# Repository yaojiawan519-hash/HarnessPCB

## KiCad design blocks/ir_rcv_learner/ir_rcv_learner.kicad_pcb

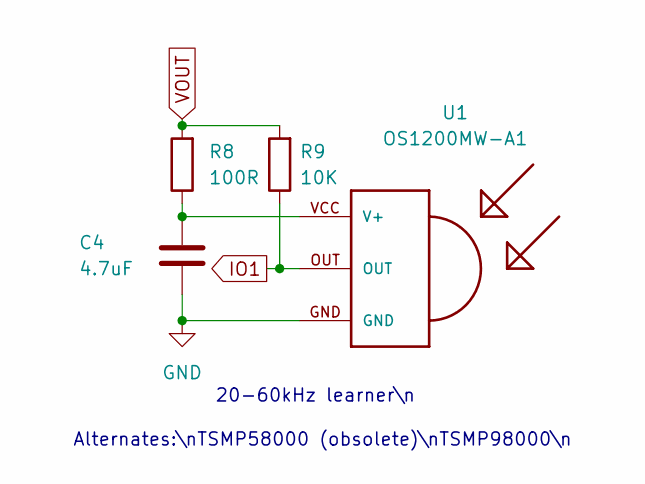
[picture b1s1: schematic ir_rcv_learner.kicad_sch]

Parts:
C4: 4.7uF; C_0805_2012Metric
R8: 100R; R_0805_2012Metric
R9: 10K; R_0805_2012Metric
U1: OS1200MW-A1; TSOP18XX

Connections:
GND: C4.2, U1.GND
IO1: R9.1, U1.OUT
unnamed: C4.1, R8.1, U1.VCC (V+)
VOUT: R8.2, R9.2

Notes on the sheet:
Alternates:\nTSMP58000 (obsolete)\nTSMP98000\n
20-60kHz learner\n

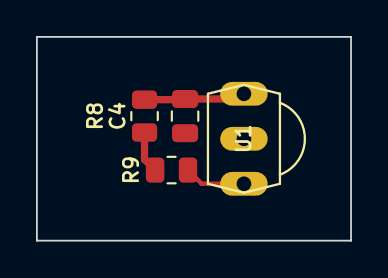
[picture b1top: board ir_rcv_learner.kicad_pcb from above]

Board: 2 copper layers, 17.5 x 11.3 mm, 4 parts (0 on the bottom side), 4 nets.

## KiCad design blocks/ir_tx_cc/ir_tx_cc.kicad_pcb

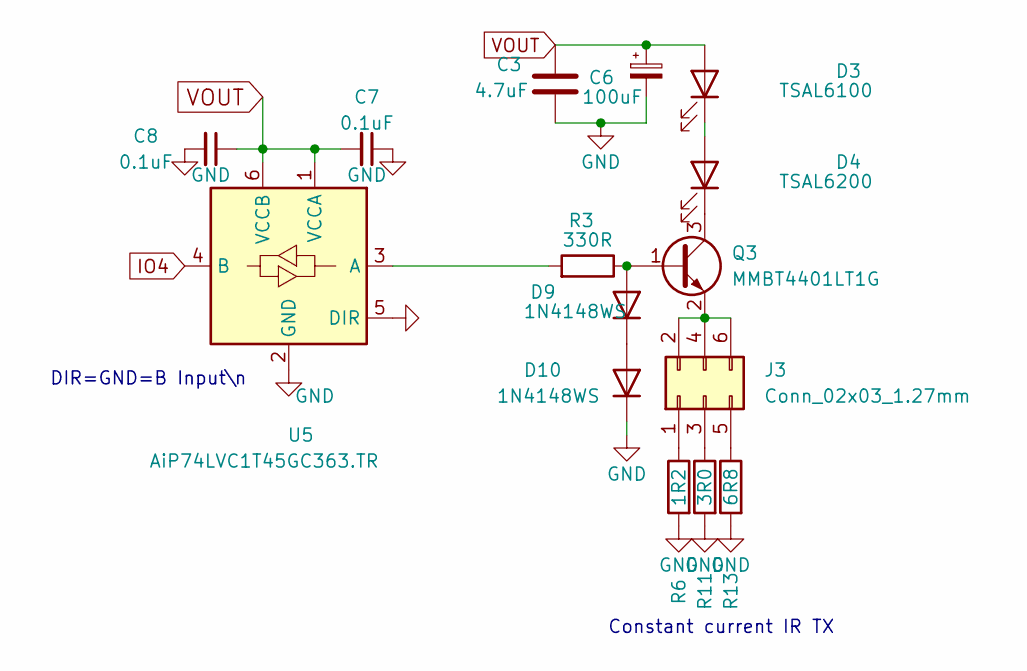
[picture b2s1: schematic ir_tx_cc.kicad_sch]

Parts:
C3: 4.7uF; C_0805_2012Metric
C6: 100uF; CP_EIA-3528-21_Kemet-B_Pad1.50x2.35mm_HandSolder
C7, C8: 0.1uF; C_0805_2012Metric
D3: TSAL6100; LED_D5.0mm_Horizontal_O1.27mm_Z3.0mm_IRGrey
D4: TSAL6200; LED_D5.0mm_Horizontal_O1.27mm_Z3.0mm_IRGrey
D9, D10: 1N4148WS; D_SOD-323F
J3: Conn_02x03_1.27mm; PinHeader_2x03_P1.27mm_Vertical
Q3: MMBT4401LT1G; SOT-23
R3: 330R; R_0805_2012Metric
R6: 1R2; R_1206_3216Metric
R11: 3R0; R_1206_3216Metric
R13: 6R8; R_1206_3216Metric
U5: AiP74LVC1T45GC363.TR; SOT-363_SC-70-6

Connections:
GND: C3.2, C6.2, C7.1, C8.2, D10.1 (K), R6.2, R11.2, R13.2, U5.2 (GND), U5.5 (DIR)
IO4: U5.4 (B)
unnamed: D3.1 (K), D4.2 (A)
unnamed: D4.1 (K), Q3.3 (C)
unnamed: D9.2 (A), Q3.1 (B), R3.1
unnamed: D9.1 (K), D10.2 (A)
unnamed: J3.1, R6.1
unnamed: J3.2, J3.4, J3.6, Q3.2 (E)
unnamed: J3.3, R11.1
unnamed: J3.5, R13.1
unnamed: R3.2, U5.3 (A)
VOUT: C3.1, C6.1, C7.2, C8.1, D3.2 (A), U5.1 (VCCA), U5.6 (VCCB)

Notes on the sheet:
Constant current IR TX
DIR=GND=B Input\n

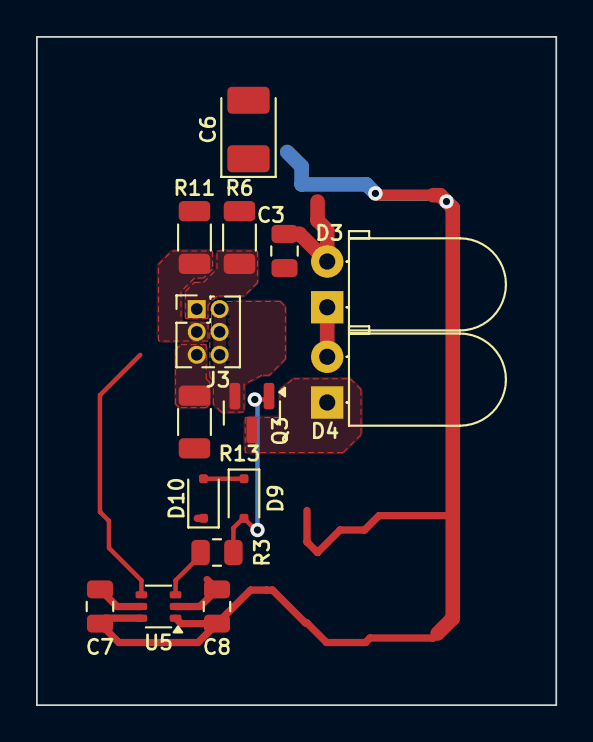
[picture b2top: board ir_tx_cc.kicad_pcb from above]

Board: 2 copper layers, 28.9 x 37.1 mm, 15 parts (0 on the bottom side), 11 nets.

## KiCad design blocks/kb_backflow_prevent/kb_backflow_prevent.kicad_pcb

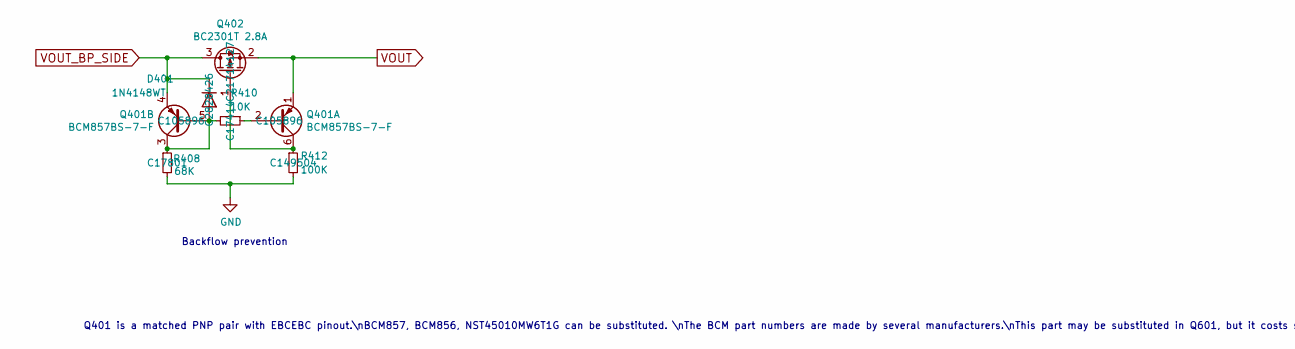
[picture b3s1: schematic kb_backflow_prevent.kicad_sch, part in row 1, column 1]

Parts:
D401: 1N4148WT; D_SOD-523
Q401: BCM857BS-7-F; SOT-363_SC-70-6
Q402: BC2301T 2.8A; SOT-523
R408: 68K; R_0805_2012Metric
R410: 10K; R_0805_2012Metric
R412: 100K; R_0805_2012Metric

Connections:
GND: R408.2, R412.2
unnamed: D401.2 (A), Q401.3 (C2), Q401.5 (B2), R408.1, R410.2
unnamed: Q401.2 (B1), R410.1
unnamed: Q401.6 (C1), Q402.1 (G), R412.1
VOUT: Q401.1 (E1), Q402.2 (S)
VOUT_BP_SIDE: D401.1 (K), Q401.4 (E2), Q402.3 (D)

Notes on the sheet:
Q401 is a matched PNP pair with EBCEBC pinout.\nBCM857, BCM856, NST45010MW6T1G can be substituted. \nThe BCM part numbers are made by several manufacturers.\nThis part may be substituted in Q601, but it costs significantly more.\n\nDMMT3906, PMP5201, PMP5501 are similar but have a BBCEEC pinout.\nT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
Backflow prevention

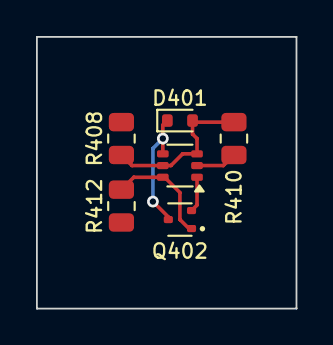
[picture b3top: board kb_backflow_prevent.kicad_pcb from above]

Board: 2 copper layers, 14.4 x 15.1 mm, 6 parts (0 on the bottom side), 6 nets.

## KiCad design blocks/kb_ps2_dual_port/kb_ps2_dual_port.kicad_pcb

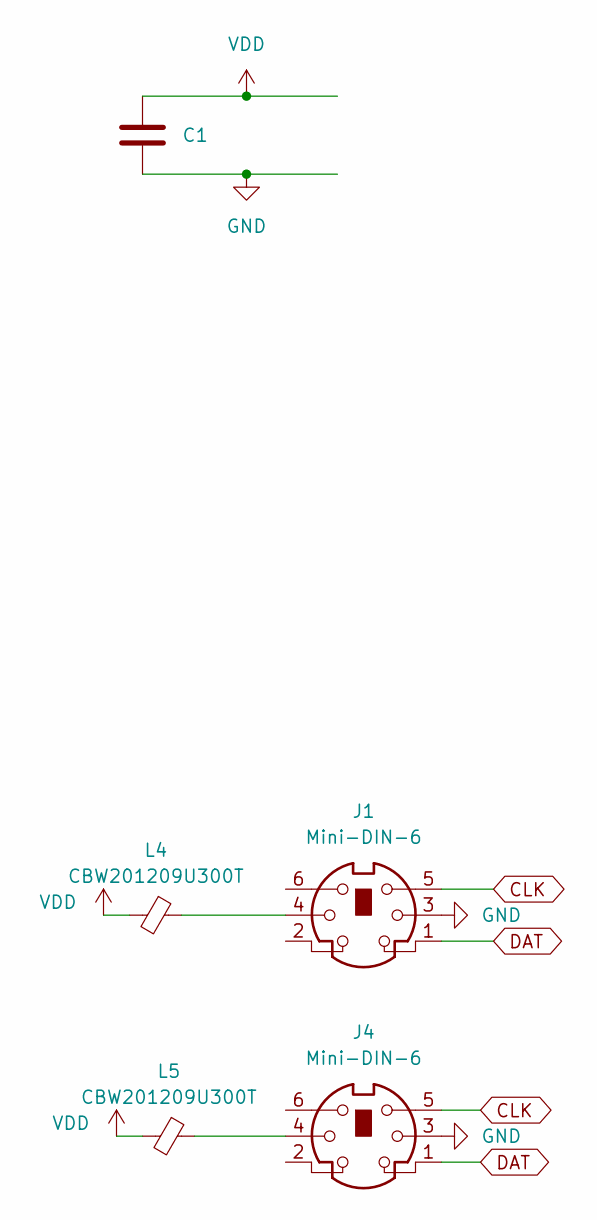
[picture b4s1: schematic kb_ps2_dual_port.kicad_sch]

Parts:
C1: 47uF/CL21A226MAYNNNE; C_0805_2012Metric
J1, J4: Mini-DIN-6; Connector_Mini-DIN_Female_6Pin_2rows
L4, L5: CBW201209U300T; L_0805_2012Metric

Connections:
CLK: J1.5, J4.5
DAT: J1.1, J4.1
GND: C1.2, J1.3, J4.3
unnamed: J1.4, L4.1
unnamed: J4.4, L5.1
VDD: C1.1, L4.2, L5.2

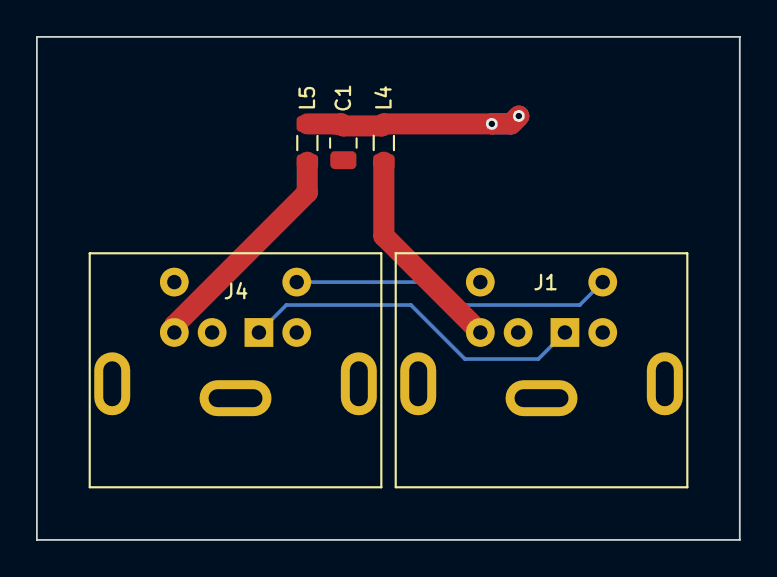
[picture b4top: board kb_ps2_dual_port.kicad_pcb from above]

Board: 2 copper layers, 39.0 x 27.9 mm, 5 parts (0 on the bottom side), 6 nets.
